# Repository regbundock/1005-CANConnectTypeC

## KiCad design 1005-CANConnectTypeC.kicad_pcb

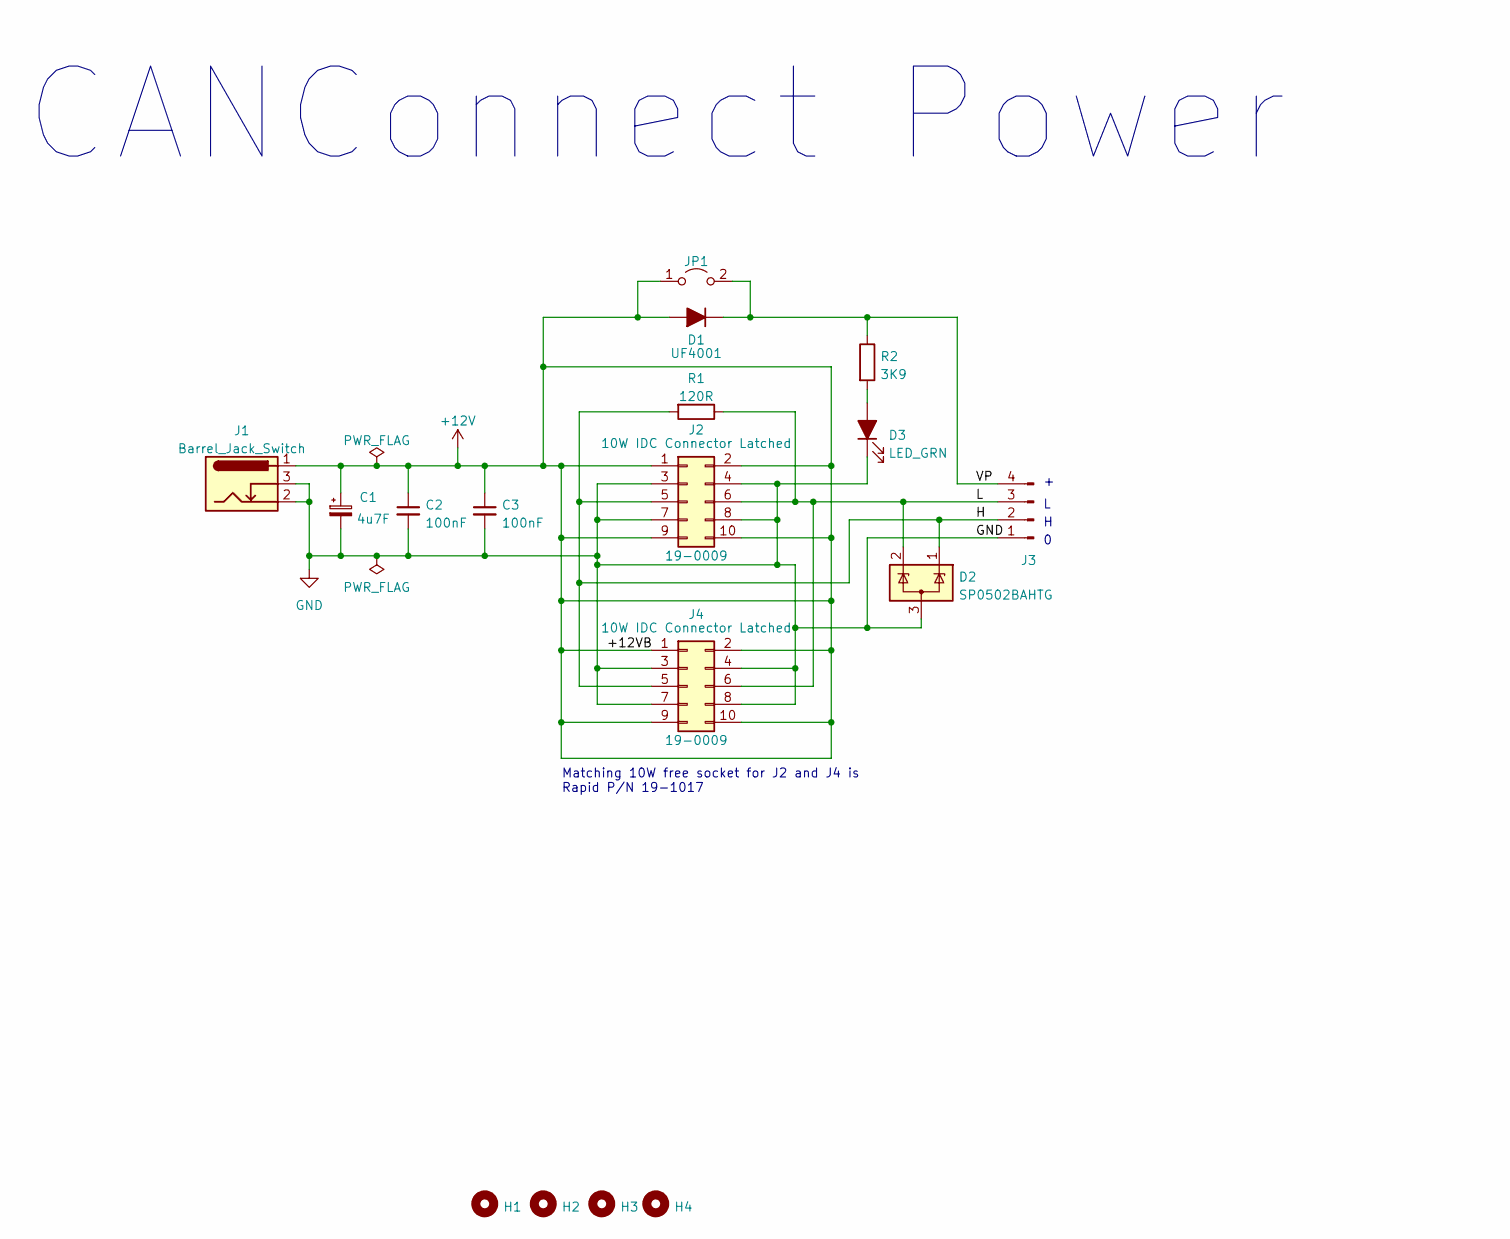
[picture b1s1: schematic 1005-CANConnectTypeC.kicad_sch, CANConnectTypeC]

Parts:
C1: 4u7F; CP_Radial_Tantal_D4.5mm_P2.50mm
C2, C3: 100nF; C_Disc_D4.3mm_W1.9mm_P5.00mm
D1: UF4001; D_DO-41_SOD81_P10.16mm_Horizontal
D2: SP0502BAHTG; SOT-23
D3: LED_GRN; LED_D3.0mm
H1, H2, H3, H4: MountingHole; MountingHole_3.2mm_M3_DIN965_Pad_TopBottom
J1: Barrel_Jack_Switch; BarrelJack_Wuerth_6941xx301002
J2, J4: 10W IDC Connector Latched; IDC-Header_2x05_P2.54mm_Latch_Vertical; Part No. 19-0009
J3: Conn_01x04_Male; Camdenboss_3pt5mm_pitch_PCB_horizontal_4Way
JP1: Jumper_2_Open; PinHeader_1x02_P2.54mm_Vertical
R1: 120R; R_Axial_P10.16mm_Horizontal
R2: 3K9; R_Axial_P10.16mm_Horizontal

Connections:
+12V: C1.1, C2.1, C3.1, D1.2 (A), J1.1, J2.1, J2.2, J2.9, J2.10, J4.1, J4.2, J4.9, J4.10, JP1.1 (A)
/H: D2.1 (K), J2.5, J3.2, J4.5, R1.2
/L: D2.2 (K), J2.6, J3.3, J4.6, R1.1
/VP: D1.1 (K), J3.4, JP1.2 (B), R2.1
GND: C1.2, C2.2, C3.2, D2.3 (A), D3.1 (K), J1.2, J1.3, J2.3, J2.4, J2.7, J2.8, J3.1, J4.3, J4.4, J4.7, J4.8
unnamed: D3.2 (A), R2.2

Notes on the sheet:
CANConnect Power
Matching 10W free socket for J2 and J4 is Rapid P/N 19-1017

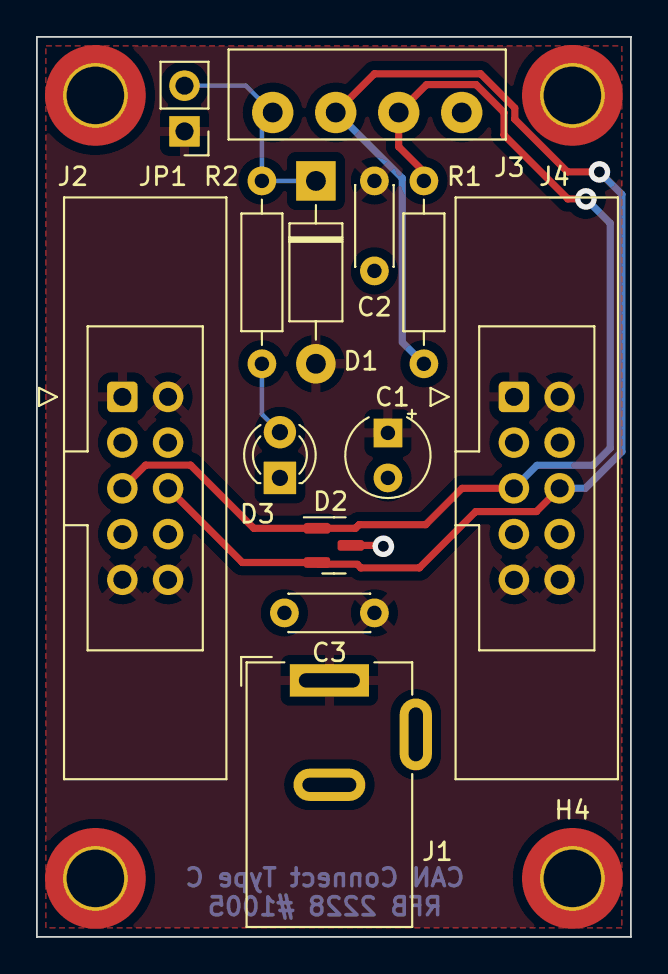
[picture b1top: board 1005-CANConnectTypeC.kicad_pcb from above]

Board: 2 copper layers, 33.0 x 50.0 mm, 17 parts (0 on the bottom side), 6 nets.

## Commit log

2022-09-22 second commit
